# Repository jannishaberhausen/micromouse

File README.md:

# SPEEDY GONZALES - A MICROMOUSE PROJECT
## Don't Call It Micromouse - Call It Megamouse
### Ever wondered what Speedy Gonzales does nowadys?

---

**From Wikipedia:**
Micromouse is an event where small robot mice solve a 16×16 maze. It began in the late 1970s. Events are held worldwide, and are most popular in the UK, U.S., Japan, Singapore, India, South Korea and becoming popular in subcontinent countries such as Sri Lanka.

The maze is made up of a 16×16 grid of cells, each 180 mm square with walls 50 mm high. The mice are completely autonomous robots that must find their way from a predetermined starting position to the central area of the maze unaided. The mouse needs to keep track of where it is, discover walls as it explores, map out the maze and detect when it has reached the goal. Having reached the goal, the mouse will typically perform additional searches of the maze until it has found an optimal route from the start to the finish. Once the optimal route has been found, the mouse will run that route in the shortest possible time.

Competitions and conferences are still run regularly.

----

Watch a video of Speedy Gonzales in action [here](https://youtu.be/TwjPslRqBsg).

### Getting Started

Notice `main.c` starts the T1 timer `startTimer()` and the finite state machine (FSM) `plannerFSM()` which realizes the planning of mouse motions before running in an infinite loop in which the behaviour is controlled by the planning FSM and the motion FSM which in turn is called every 50 ms by a timer interupt in T1 (see `timer.c`).
    
The most important motions (and their respective controllers) are defined in `mouse_motion.c` and the business logic for the path planning is implemented in `pathfinder.c`.

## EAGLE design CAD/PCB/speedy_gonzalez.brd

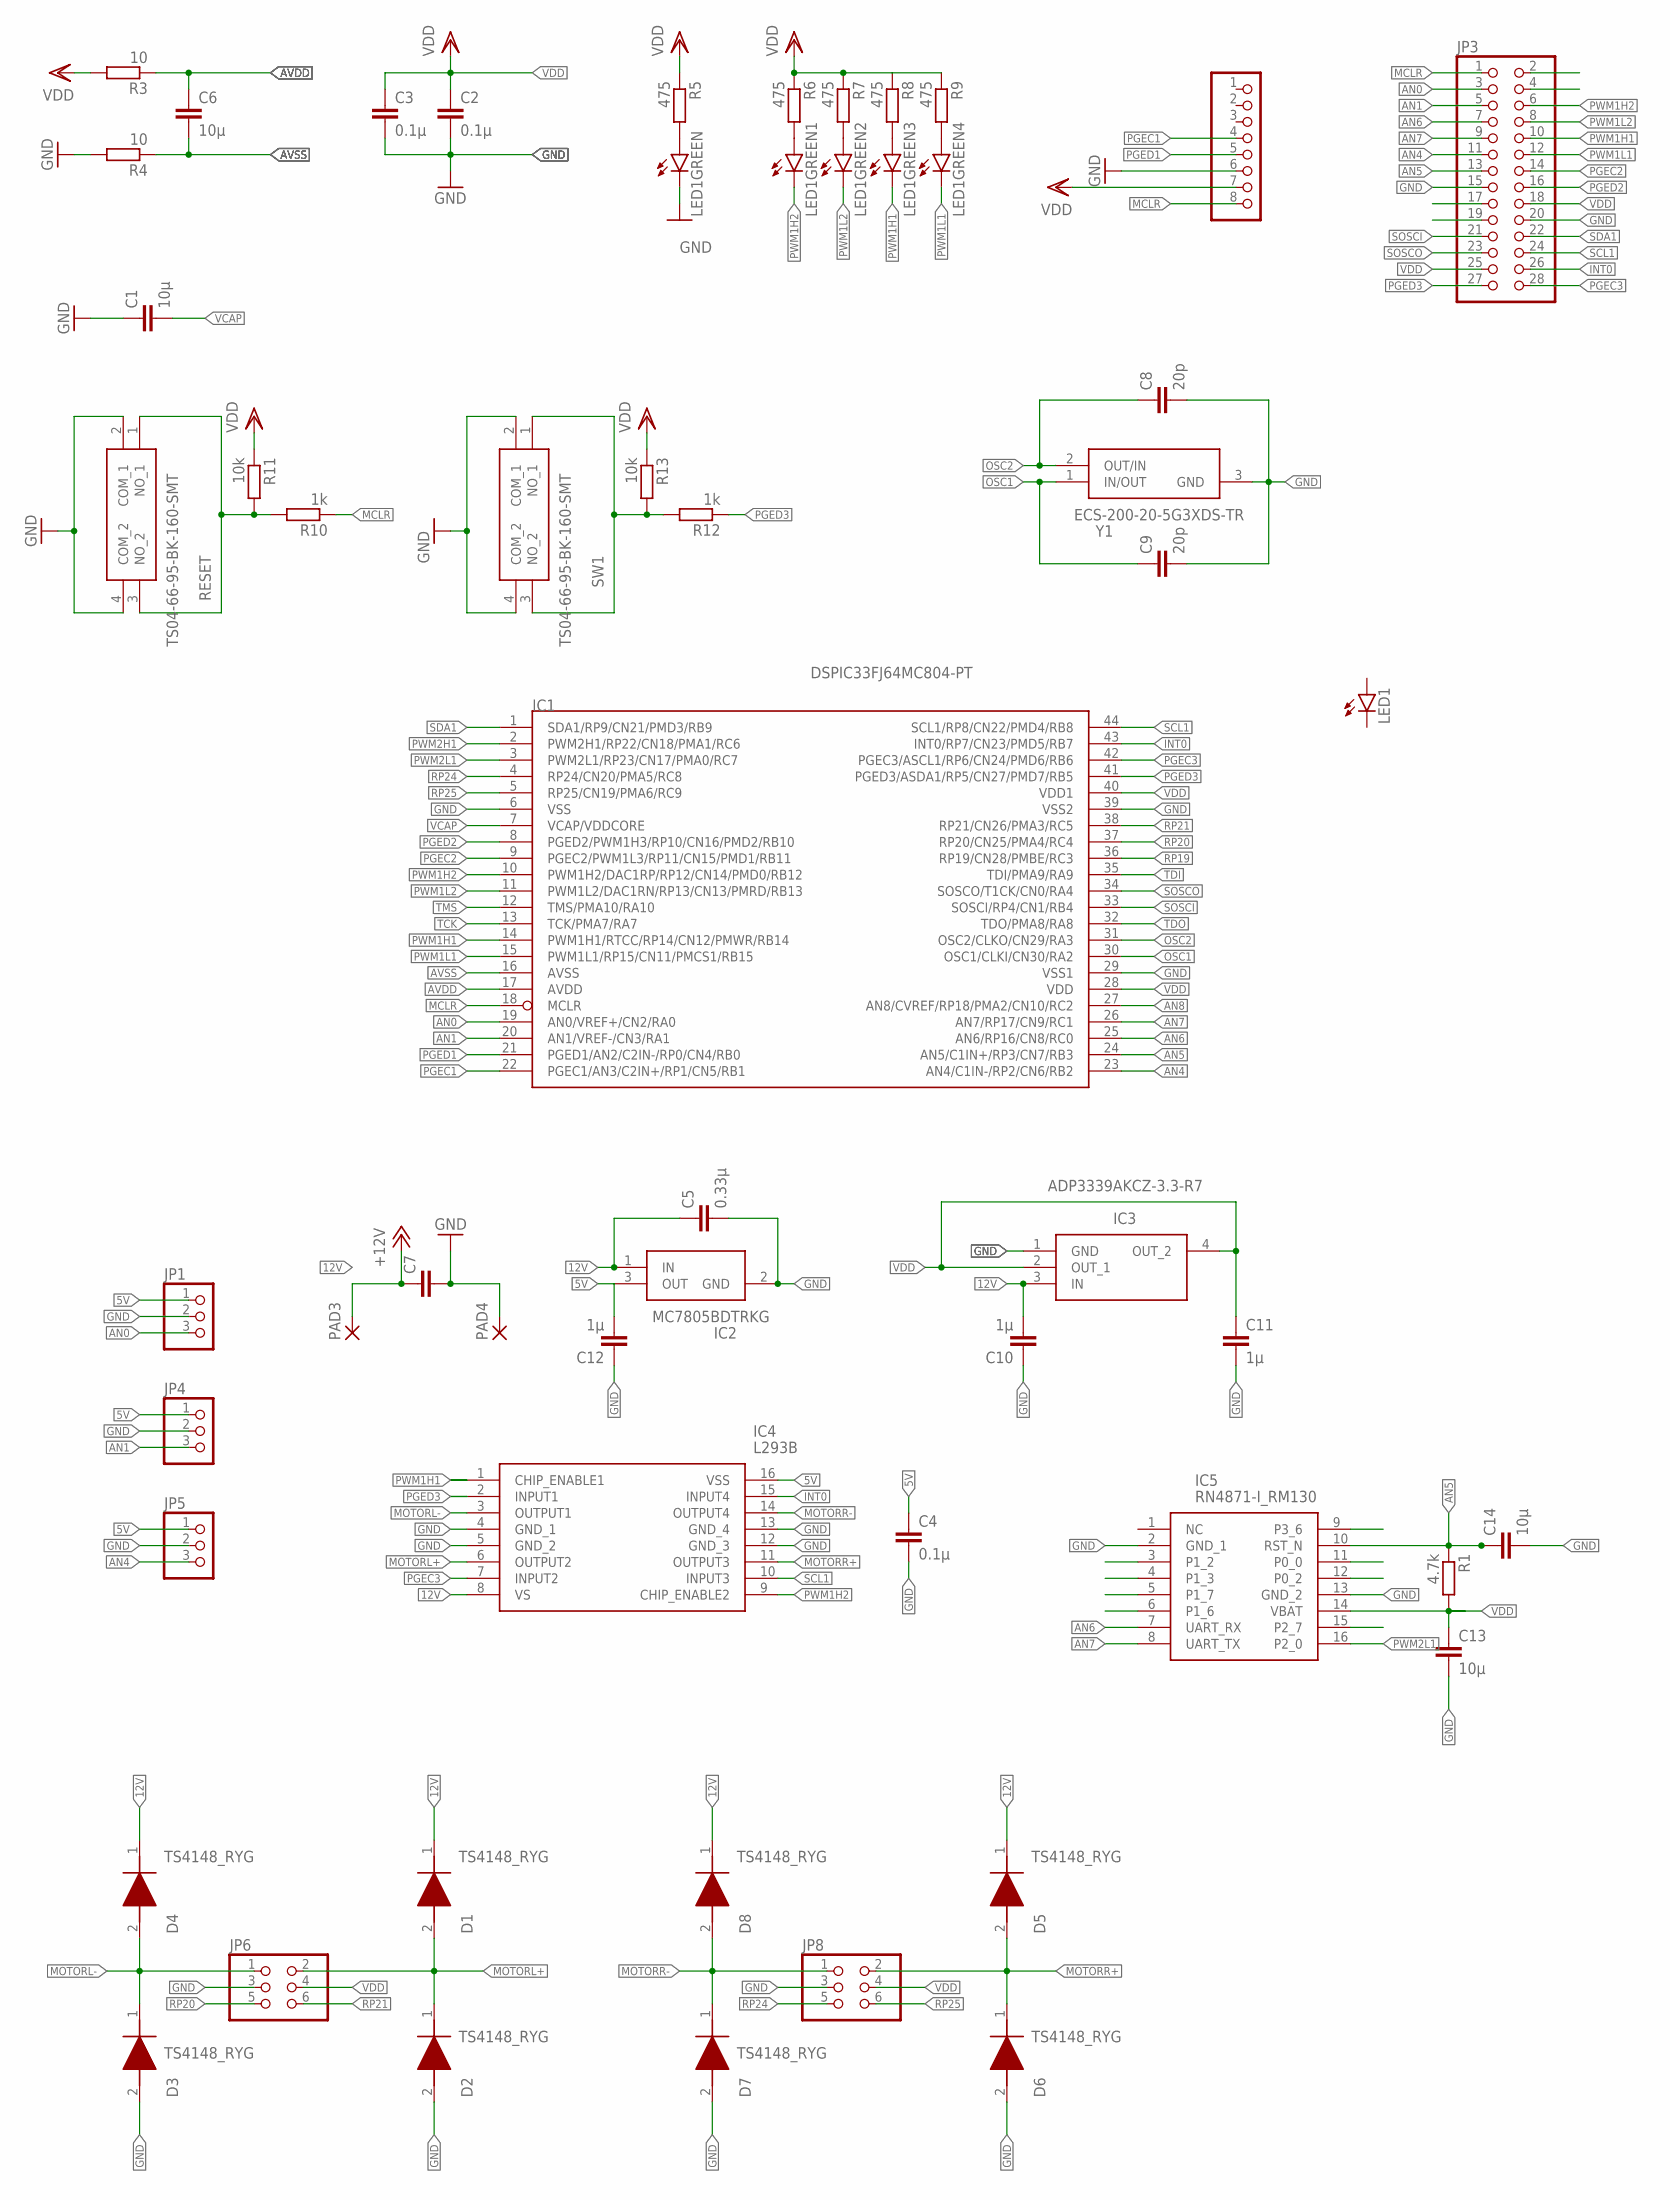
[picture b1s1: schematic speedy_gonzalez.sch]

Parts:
C1, C6, C13, C14: 10µ; C0805
C2, C3, C4: 0.1µ; C0805
C5: 0.33µ; C0805
C7: C-EU050-055X075; C050-055X075
C8, C9: 20p; C0805
C10, C11, C12: 1µ; C0805
D1, D2, D3, D4, D5, D6, D7, D8: TS4148_RYG; DIOC2012X85N
IC1: DSPIC33FJ64MC804-PT; TQFP44
IC2: MC7805BDTRKG; LM317MADTRKG
IC3: ADP3339AKCZ-3.3-R7; SOT230P700X180-4N
IC4: L293B; DIP850W50P254L2000H510Q16N
IC5: RN4871-I_RM130; RN4871
JP1, JP4, JP5: PINHD-1X3; 1X03
JP2: PINHD-1X8; 1X08
JP3: PINHD-2X14; 2X14
JP6, JP8: PINHD-2X3; 2X03
LED1: LED5MM
LED1GREEN, LED1GREEN1, LED1GREEN2, LED1GREEN3, LED1GREEN4: LEDCHIPLED_0805; CHIPLED_0805
PAD3, PAD4: 2,15/1,0
R1: 4.7k; R0805
R3, R4: 10; R0805
R5, R6, R7, R8, R9: 475; R0805
R10, R12: 1k; R0805
R11, R13: 10k; R0805
RESET: TS04-66-95-BK-160-SMT; TS046695BK160SMT
SW1: TS04-66-95-BK-160-SMT; TS046695BK160SMT
Y1: ECS-200-20-5G3XDS-TR; ECS250205G3XDSFTR

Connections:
5V: C4.1, C12.2, IC2.3 (OUT), IC4.16 (VSS), JP1.1, JP4.1, JP5.1
12V: C5.1, C7.1, C10.2, D1.1 (K), D4.1 (K), D5.1 (K), D8.1 (K), IC2.1 (IN), IC3.3 (IN), IC4.8 (VS), PAD3.1
AN0: IC1.19 (AN0/VREF+/CN2/RA0), JP1.3, JP3.3
AN1: IC1.20 (AN1/VREF-/CN3/RA1), JP3.5, JP4.3
AN4: IC1.23 (AN4/C1IN-/RP2/CN6/RB2), JP3.11, JP5.3
AN5: C14.1, IC1.24 (AN5/C1IN+/RP3/CN7/RB3), IC5.10 (RST_N), JP3.13, R1.1
AN6: IC1.25 (AN6/RP16/CN8/RC0), IC5.7 (UART_RX), JP3.7
AN7: IC1.26 (AN7/RP17/CN9/RC1), IC5.8 (UART_TX), JP3.9
AN8: IC1.27 (AN8/CVREF/RP18/PMA2/CN10/RC2)
AVDD: C6.1, IC1.17 (AVDD), R3.1
AVSS: C6.2, IC1.16 (AVSS), R4.1
GND: C1.1, C2.2, C3.2, C4.2, C5.2, C7.2, C8.2, C9.2, C10.1, C11.2, C12.1, C13.2, C14.2, D2.2 (A), D3.2 (A), D6.2 (A), D7.2 (A), IC1.6 (VSS), IC1.29 (VSS1), IC1.39 (VSS2), IC2.2 (GND), IC3.1 (GND), IC4.4 (GND_1), IC4.5 (GND_2), IC4.12 (GND_3), IC4.13 (GND_4), IC5.2 (GND_1), IC5.13 (GND_2), JP1.2, JP2.6, JP3.15, JP3.20, JP4.2, JP5.2, JP6.3, JP8.3, LED1GREEN.C, PAD4.1, R4.2, RESET.2 (COM_1), RESET.4 (COM_2), SW1.2 (COM_1), SW1.4 (COM_2), Y1.3 (GND)
INT0: IC1.43 (INT0/RP7/CN23/PMD5/RB7), IC4.15 (INPUT4), JP3.26
MCLR: IC1.18 (MCLR), JP2.8, JP3.1, R10.1
MOTORL+: D1.2 (A), D2.1 (K), IC4.6 (OUTPUT2), JP6.2
MOTORL-: D3.1 (K), D4.2 (A), IC4.3 (OUTPUT1), JP6.1
MOTORR+: D5.2 (A), D6.1 (K), IC4.11 (OUTPUT3), JP8.2
MOTORR-: D7.1 (K), D8.2 (A), IC4.14 (OUTPUT4), JP8.1
unnamed: LED1GREEN.A, R5.2
unnamed: LED1GREEN1.A, R6.2
unnamed: LED1GREEN2.A, R7.2
unnamed: LED1GREEN3.A, R8.2
unnamed: R12.2, R13.2, SW1.1 (NO_1), SW1.3 (NO_2)
unnamed: R10.2, R11.2, RESET.1 (NO_1), RESET.3 (NO_2)
unnamed: LED1GREEN4.A, R9.2
OSC1: C9.1, IC1.30 (OSC1/CLKI/CN30/RA2), Y1.1 (IN/OUT)
OSC2: C8.1, IC1.31 (OSC2/CLKO/CN29/RA3), Y1.2 (OUT/IN)
PGEC1: IC1.22 (PGEC1/AN3/C2IN+/RP1/CN5/RB1), JP2.4
PGEC2: IC1.9 (PGEC2/PWM1L3/RP11/CN15/PMD1/RB11), JP3.14
PGEC3: IC1.42 (PGEC3/ASCL1/RP6/CN24/PMD6/RB6), IC4.7 (INPUT2), JP3.28
PGED1: IC1.21 (PGED1/AN2/C2IN-/RP0/CN4/RB0), JP2.5
PGED2: IC1.8 (PGED2/PWM1H3/RP10/CN16/PMD2/RB10), JP3.16
PGED3: IC1.41 (PGED3/ASDA1/RP5/CN27/PMD7/RB5), IC4.2 (INPUT1), JP3.27, R12.1
PWM1H1: IC1.14 (PWM1H1/RTCC/RP14/CN12/PMWR/RB14), IC4.1 (CHIP_ENABLE1), JP3.10, LED1GREEN3.C
PWM1H2: IC1.10 (PWM1H2/DAC1RP/RP12/CN14/PMD0/RB12), IC4.9 (CHIP_ENABLE2), JP3.6, LED1GREEN1.C
PWM1L1: IC1.15 (PWM1L1/RP15/CN11/PMCS1/RB15), JP3.12, LED1GREEN4.C
PWM1L2: IC1.11 (PWM1L2/DAC1RN/RP13/CN13/PMRD/RB13), JP3.8, LED1GREEN2.C
PWM2H1: IC1.2 (PWM2H1/RP22/CN18/PMA1/RC6)
PWM2L1: IC1.3 (PWM2L1/RP23/CN17/PMA0/RC7), IC5.16 (P2_0)
RP19: IC1.36 (RP19/CN28/PMBE/RC3)
RP20: IC1.37 (RP20/CN25/PMA4/RC4), JP6.5
RP21: IC1.38 (RP21/CN26/PMA3/RC5), JP6.6
RP24: IC1.4 (RP24/CN20/PMA5/RC8), JP8.5
RP25: IC1.5 (RP25/CN19/PMA6/RC9), JP8.6
SCL1: IC1.44 (SCL1/RP8/CN22/PMD4/RB8), IC4.10 (INPUT3), JP3.24
SDA1: IC1.1 (SDA1/RP9/CN21/PMD3/RB9), JP3.22
SOSCI: IC1.33 (SOSCI/RP4/CN1/RB4), JP3.21
SOSCO: IC1.34 (SOSCO/T1CK/CN0/RA4), JP3.23
TCK: IC1.13 (TCK/PMA7/RA7)
TDI: IC1.35 (TDI/PMA9/RA9)
TDO: IC1.32 (TDO/PMA8/RA8)
TMS: IC1.12 (TMS/PMA10/RA10)
VCAP: C1.2, IC1.7 (VCAP/VDDCORE)
VDD: C2.1, C3.1, C11.1, C13.1, IC1.28 (VDD), IC1.40 (VDD1), IC3.2 (OUT_1), IC3.4 (OUT_2), IC5.14 (VBAT), JP2.7, JP3.18, JP3.25, JP6.4, JP8.4, R1.2, R3.2, R5.1, R6.1, R7.1, R8.1, R9.1, R11.1, R13.1

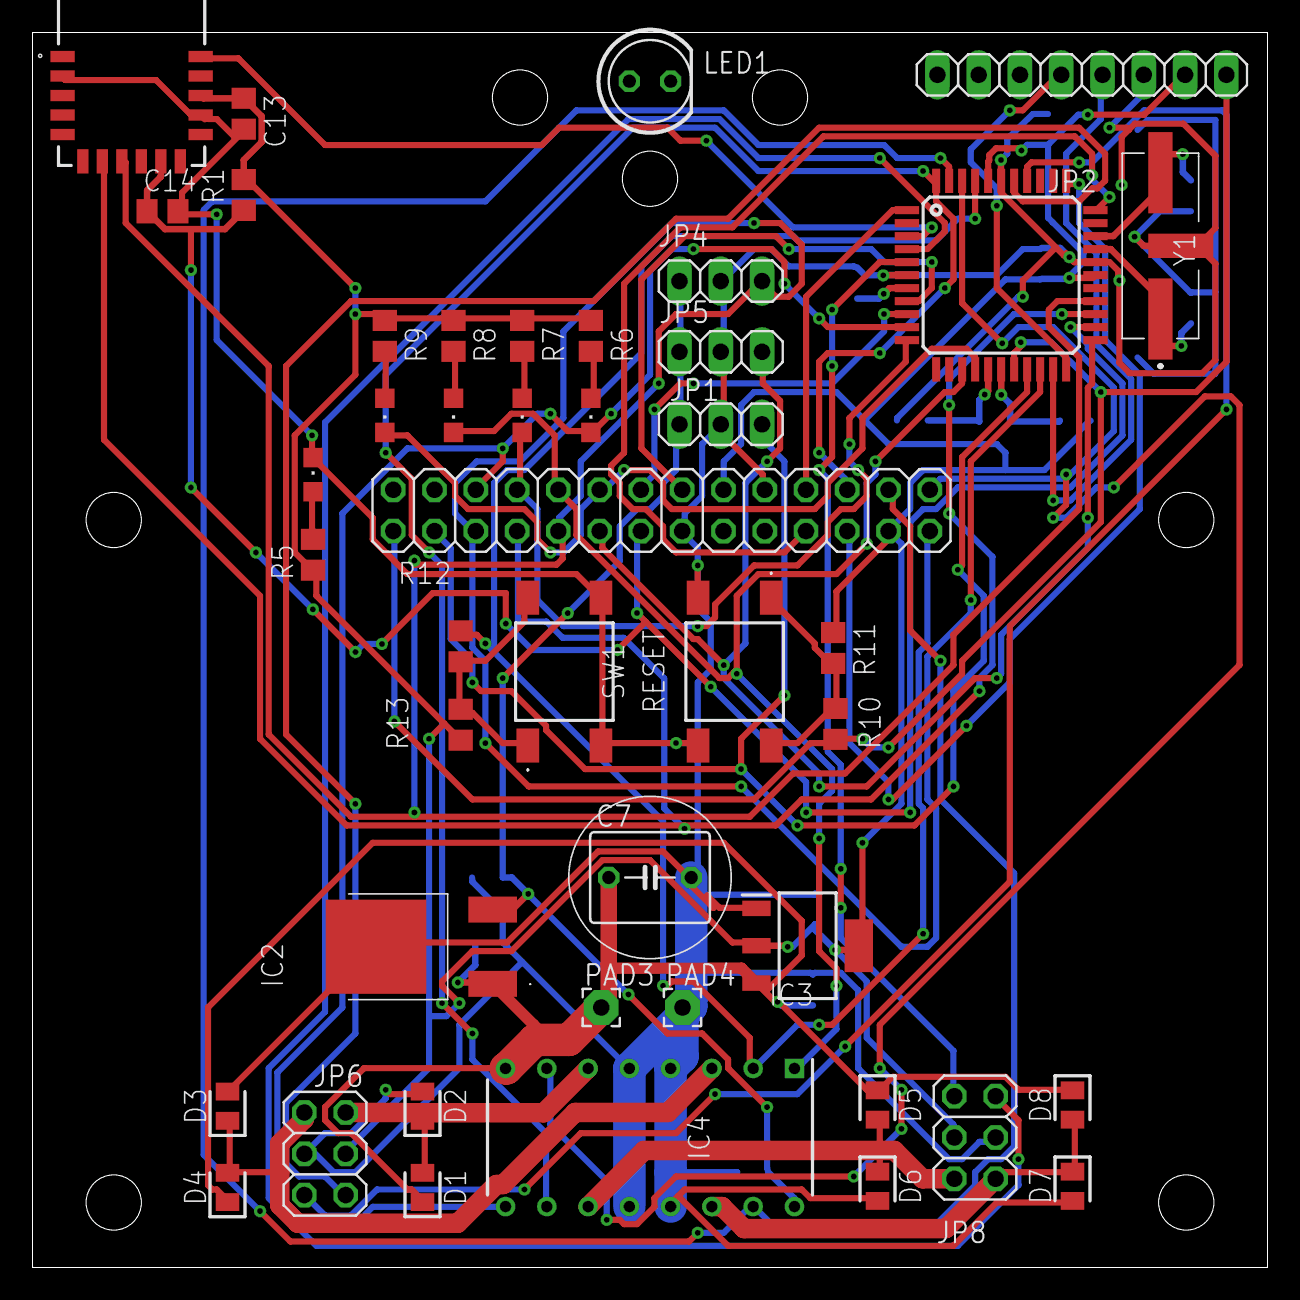
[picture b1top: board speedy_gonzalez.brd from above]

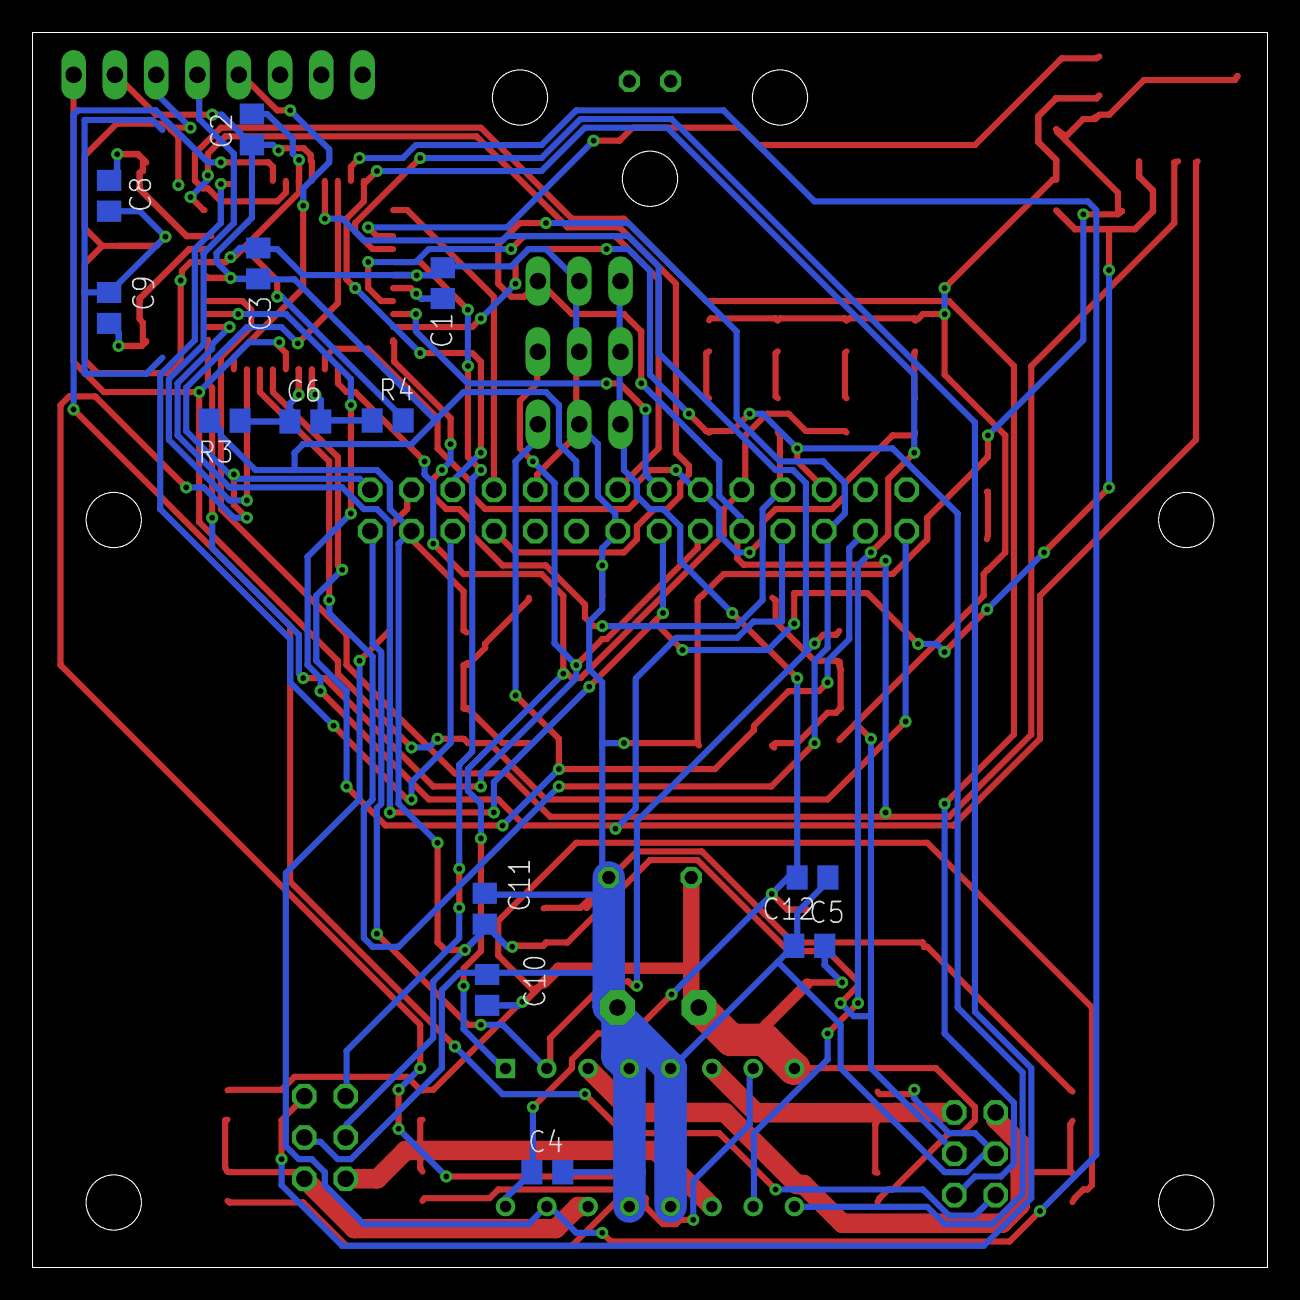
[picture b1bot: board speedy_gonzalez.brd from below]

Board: 2 copper layers, 76.0 x 76.0 mm, 57 parts (13 on the bottom side), 47 nets.

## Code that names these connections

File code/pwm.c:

#include <xc.h>

#include "pwm.h"
#include "IOconfig.h"


/**
 * set up PWM1
 * 
 * Uses a frequency of 250Hz.
 */
void initPWM()
{
    /* 
     * PWM1:
     * Using FCY = 40MHz, FPWM = 250Hz, the base time is
     * P1TPER = FCY / (FPWM * TCKPS) -1 = 9999
     * where the prescale TCKPS=16 is chosen to fit P1TPER into 15bit.
     */
    P1TCONbits.PTEN = 0; // Switch off PWM generator
    P1TCONbits.PTCKPS = 0b10; // Sets prescaler, available are 1(00),4(01),16(10) or 64(11)
    P1TPER = 9999; //15 bit register (Time Base Period )
    PWM1CON1bits.PMOD1 = 1; // set PWM unit 1 to independent mode
    PWM1CON1bits.PMOD2 = 1;
    PWM1CON1bits.PMOD3 = 1;
    // diable all PWM pins
    PWM1CON1bits.PEN1H = 0; // disable PWM driver PWM1H1 (MOTORL, LED1)
    PWM1CON1bits.PEN2H = 0; // disable PWM driver PWM1H2 (MOTORR, LED3)
    PWM1CON1bits.PEN3H = 0; // disable PWM driver
    PWM1CON1bits.PEN1L = 0; // disable PWM driver PWM1L1 (LED2)
    PWM1CON1bits.PEN2L = 0; // disable PWM driver PWM1L2 (LED4)
    PWM1CON1bits.PEN3L = 0; // disable PWM driver

    P1TCONbits.PTEN = 1; // Switch on PWM generator
    // zero duty cycle initially
    P1DC1 = 0;
    P1DC2 = 0;
    P1DC3 = 0;
}

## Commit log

2022-06-08 added README.md
2022-06-15 incomplete pathfinding implementation
2022-06-19 experimenting with linked lists
2022-06-22 exploit phase, start of test framework
2022-06-26 complete tests, minor bugfixes
2022-07-20 add sensor functions
2022-07-20 add acd / dma setup
2022-08-23 Add simplified higher-level setup functions, workaround for pin collision, and hardware tests; some cleaning up
2022-08-23 Use internal pullup (commented out)
2022-08-23 fix possible write to CN pin
2022-08-26 changed testSwitch, toggle in timer interrupt (not cn)
2022-08-31 fix motor test case
2022-09-13 fix sensor pins, motors, and switch setup
2022-09-15 motion tests
2022-09-15 some test cases for the motors, encoders, and sensors
2022-09-15 push some stuff i forgot last time
2022-09-16 added some new tests
2022-09-18 added pcb files
2022-09-18 new function format. separated hw and mouse tests. moved motion functions to separate file
2022-09-19 reformated some more test cases
2022-09-21 Add tests for PID control, nested control, and main loop
2022-10-01 some restructuring
2022-10-01 update tests
2022-10-01 more forward control, bugfixes
2022-10-01 changes to test and motion funcs
2022-10-03 FSM, pathfinder integration
2022-10-06 optimize exploration, first cleanup
2022-10-06 3d print parts, stl, dwg, pdf
2022-10-13 integration test
2022-10-13 smooth turns
2022-10-13 explore working, exploit --> restart
2022-10-13 previous changes to merge
2022-10-13 minor changes
2022-10-14 fix turns
2022-10-14 Fix eploit phase, recalibrate on dead ends
2022-10-14 make buttons work
2022-10-14 Improved calibration
2022-10-18 controller for turns
2022-10-18 minor fixes, cleanup, video
2022-10-18 more fixes
2022-10-19 implemented race (exploit) functionalities
2022-10-19 implemented path transformation for exploit phase
2022-10-20 Race integration, improve precision, optimize pathfinder
2022-10-21 fix optimized exploit
2022-10-27 some comments
2022-10-27 repeated exploit
2022-10-27 improve race controller
2022-10-27 add save exploit phase controller
